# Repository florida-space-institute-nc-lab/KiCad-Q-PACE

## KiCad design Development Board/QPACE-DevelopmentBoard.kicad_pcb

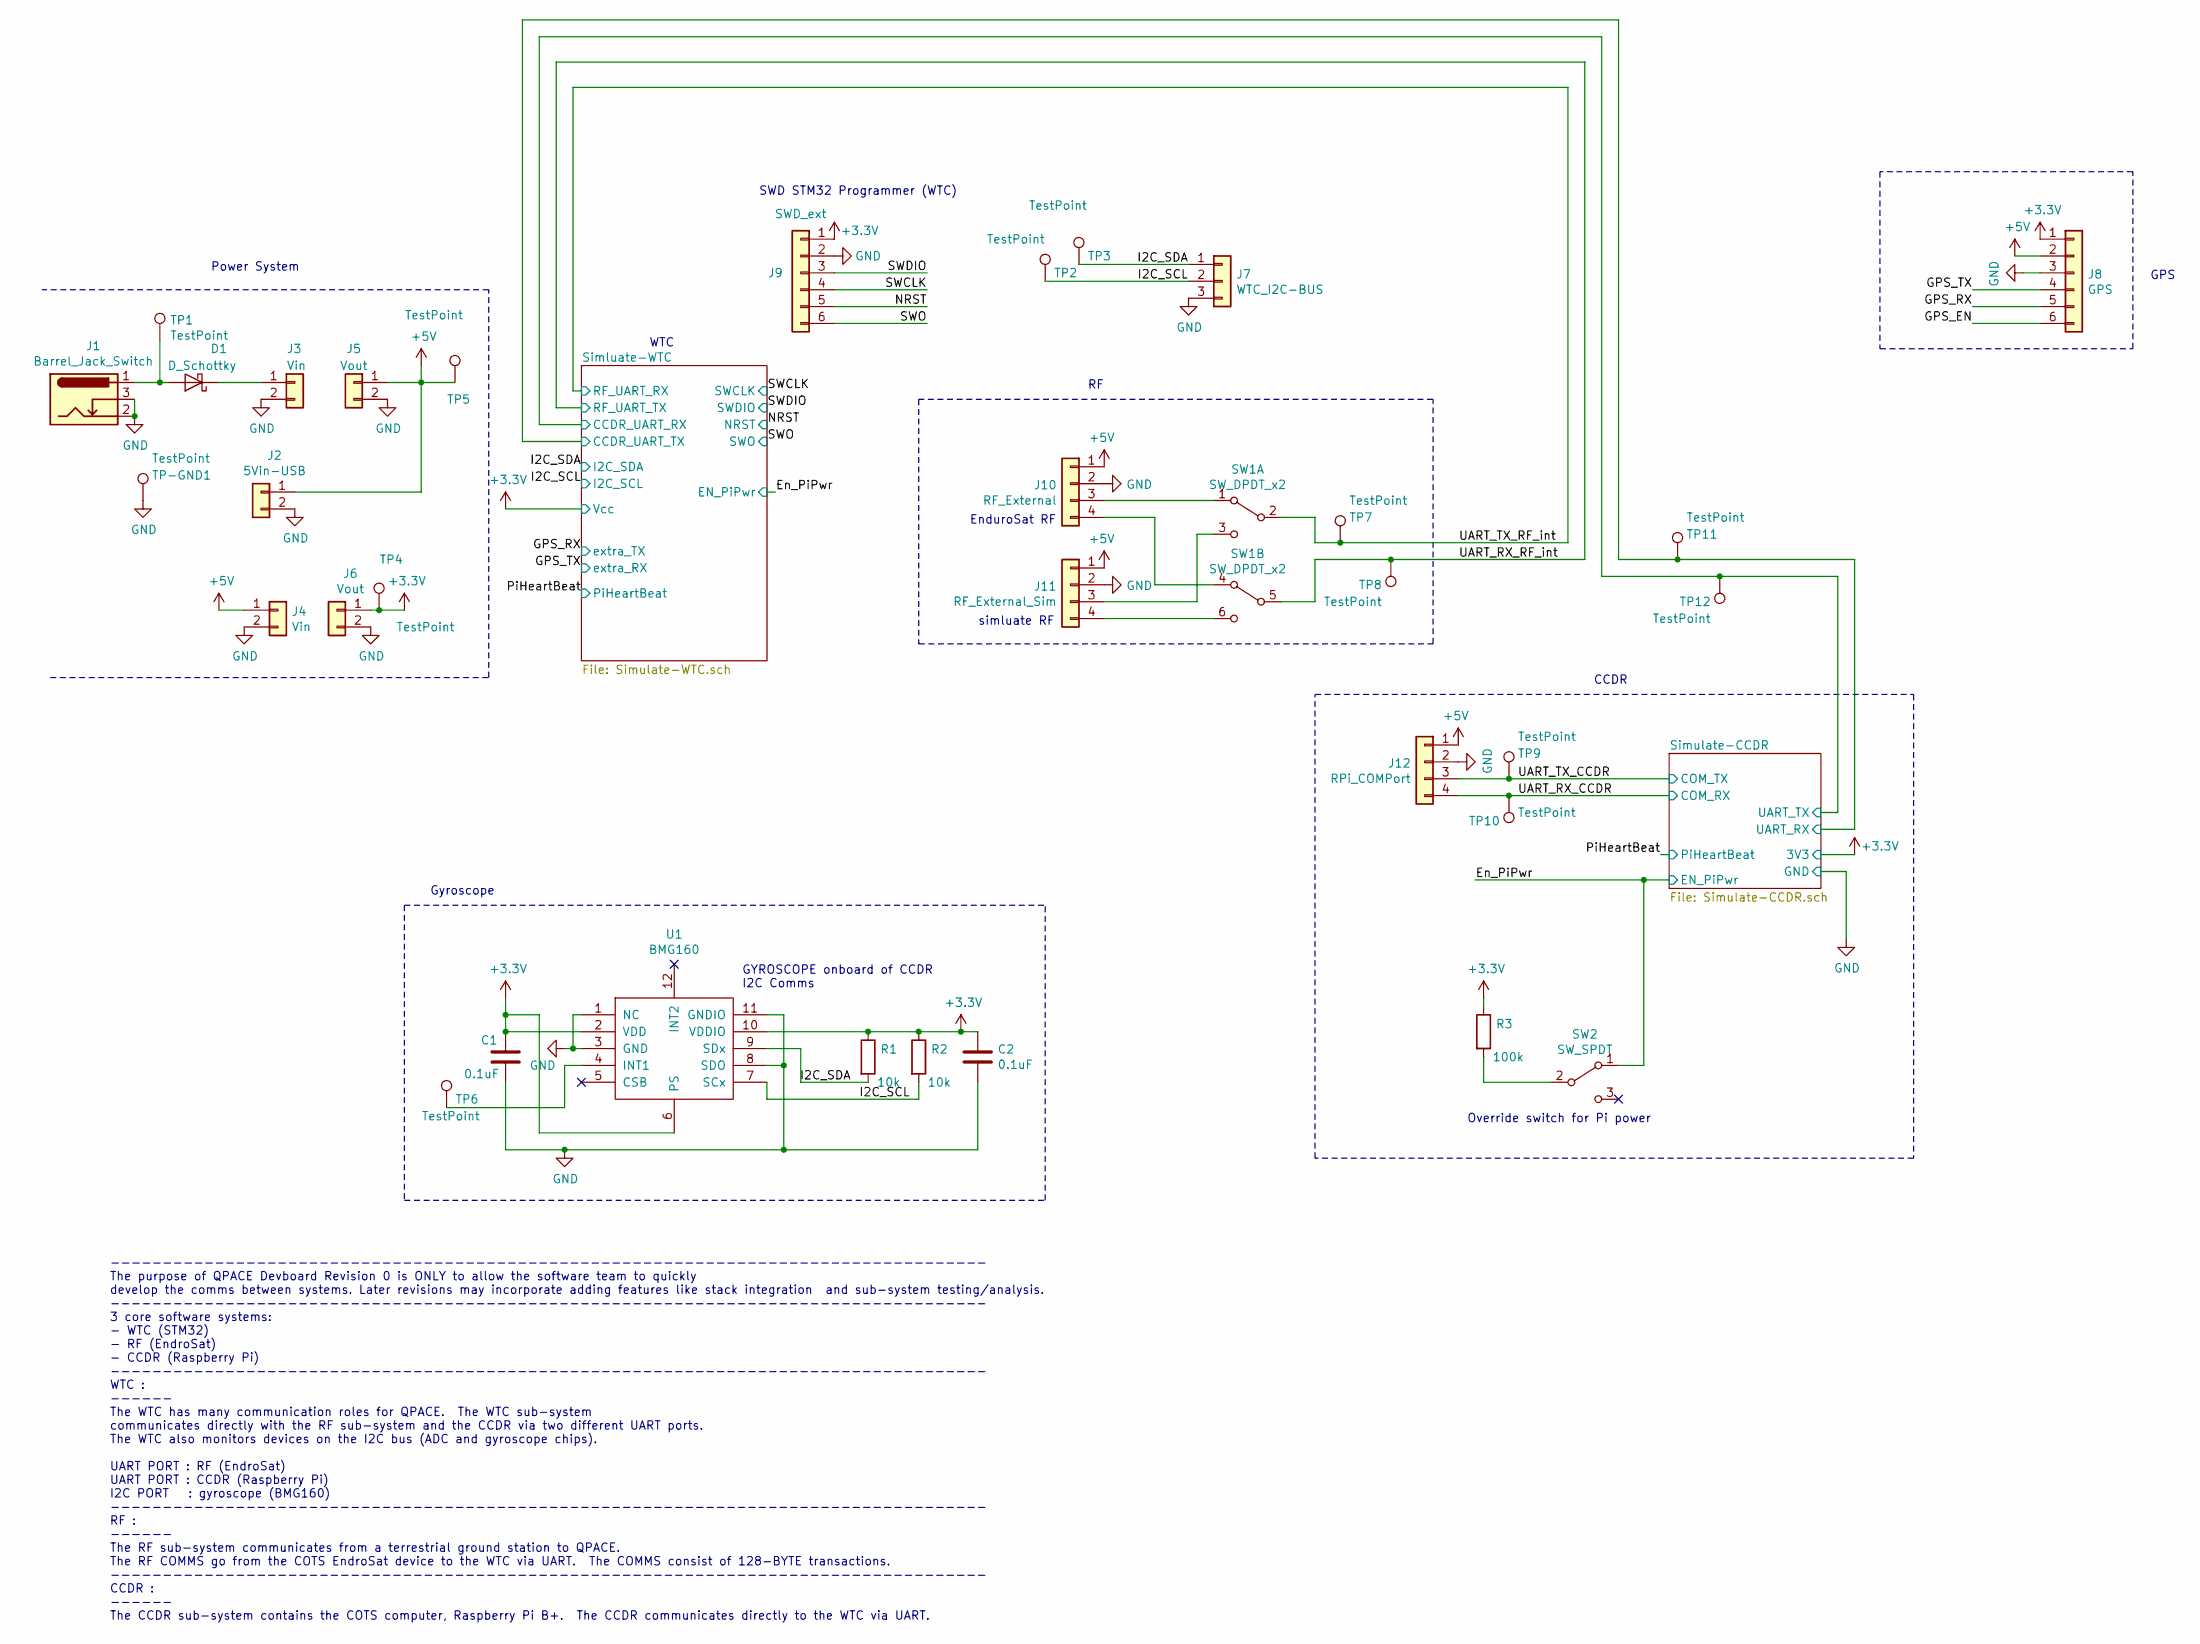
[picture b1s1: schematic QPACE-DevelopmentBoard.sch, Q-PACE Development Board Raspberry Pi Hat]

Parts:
C1, C2: 0.1uF; C_0805
D1: D_Schottky; SOD-128
J1: Barrel_Jack_Switch; TerminalBlock_Phoenix_PT-3.5mm_3pol
J2: 5Vin-USB; Socket_Strip_Straight_1x02_Pitch2.54mm
J3, J4: Vin; Socket_Strip_Straight_1x02_Pitch15.24mm
J5, J6: Vout; Socket_Strip_Straight_1x02_Pitch15.24mm
J7: WTC_I2C-BUS; Socket_Strip_Straight_1x03_Pitch2.54mm
J8: GPS; Socket_Strip_Straight_1x06_Pitch2.54mm
J9: SWD_ext; Socket_Strip_Straight_1x06_Pitch2.54mm
J10: RF_External; Socket_Strip_Straight_1x04_Pitch2.54mm
J11: RF_External_Sim; Socket_Strip_Straight_1x04_Pitch2.54mm
J12: RPi_COMPort; Socket_Strip_Straight_1x04_Pitch2.54mm
R1, R2: 10k; R_0805
R3: 100k; R_0805
SW1: SW_DPDT_x2; Pin_Header_Straight_2x03_Pitch2.54mm
SW2: SW_SPDT; Socket_Strip_Straight_1x03_Pitch2.54mm
TP1, TP2, TP3, TP4, TP5, TP6, TP7, TP8, TP9, TP10, TP11, TP12: TestPoint; Measurement_Point_Round-SMD-Pad_Small
TP-GND1: TestPoint; Measurement_Point_Round-SMD-Pad_Small
U1: BMG160; LGA-12_2x2mm_Pitch0.5mm

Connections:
3_3V_Rail: C1.1, C2.1, J6.1, J8.1, J9.1, R1.1, R2.1, R3.1, TP4.1, U1.2 (VDD), U1.6 (PS), U1.10 (VDDIO); also elsewhere on the board
+5V: J2.1, J4.1, J5.1, J8.2, J10.1, J11.1, J12.1, TP5.1; also elsewhere on the board
/En_PiPwr: SW2.1 (A); also elsewhere on the board
/GPS_RX: J8.5; also elsewhere on the board
/GPS_TX: J8.4; also elsewhere on the board
/I2C_SCL: J7.2, R2.2, TP2.1, U1.7 (SCx); also elsewhere on the board
/I2C_SDA: J7.1, R1.2, TP3.1, U1.9 (SDx); also elsewhere on the board
/NRST: J9.5; also elsewhere on the board
/SWCLK: J9.4; also elsewhere on the board
/SWDIO: J9.3; also elsewhere on the board
/SWO: J9.6; also elsewhere on the board
/Simluate-WTC/CCDR_UART_RX: TP12.1; also elsewhere on the board
/Simluate-WTC/CCDR_UART_TX: TP11.1; also elsewhere on the board
/UART_RX_CCDR: J12.4, TP10.1; also elsewhere on the board
/UART_RX_RF_int: SW1.5 (B), TP8.1; also elsewhere on the board
/UART_TX_CCDR: J12.3, TP9.1; also elsewhere on the board
/UART_TX_RF_int: SW1.2 (B), TP7.1; also elsewhere on the board
GND: C1.2, C2.2, J1.2, J1.3, J2.2, J3.2, J4.2, J5.2, J6.2, J7.3, J8.3, J9.2, J10.2, J11.2, J12.2, TP-GND1.1, U1.1 (NC), U1.3 (GND), U1.8 (SDO), U1.11 (GNDIO); also elsewhere on the board
unnamed: D1.1 (K), J3.1
unnamed: D1.2 (A), J1.1, TP1.1
unnamed: J10.3, SW1.1 (A)
unnamed: J10.4, SW1.4 (A)
unnamed: J11.3, SW1.3 (C)
unnamed: J11.4, SW1.6 (C)
unnamed: R3.2, SW2.2 (B)
unnamed: TP6.1, U1.4 (INT1)

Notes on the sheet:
simluate RF
GYROSCOPE onboard of CCDR I2C Comms
------------------------------------------------------------------------------------ The purpose of QPACE Devboard Revision 0 is ONLY to allow the software team to quickly develop the comms between systems. Later revisions may incorporate adding features like stack integration and sub-system testin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
EnduroSat RF
Power System
WTC
SWD STM32 Programmer (WTC)
CCDR
GPS
Gyroscope
Override switch for Pi power

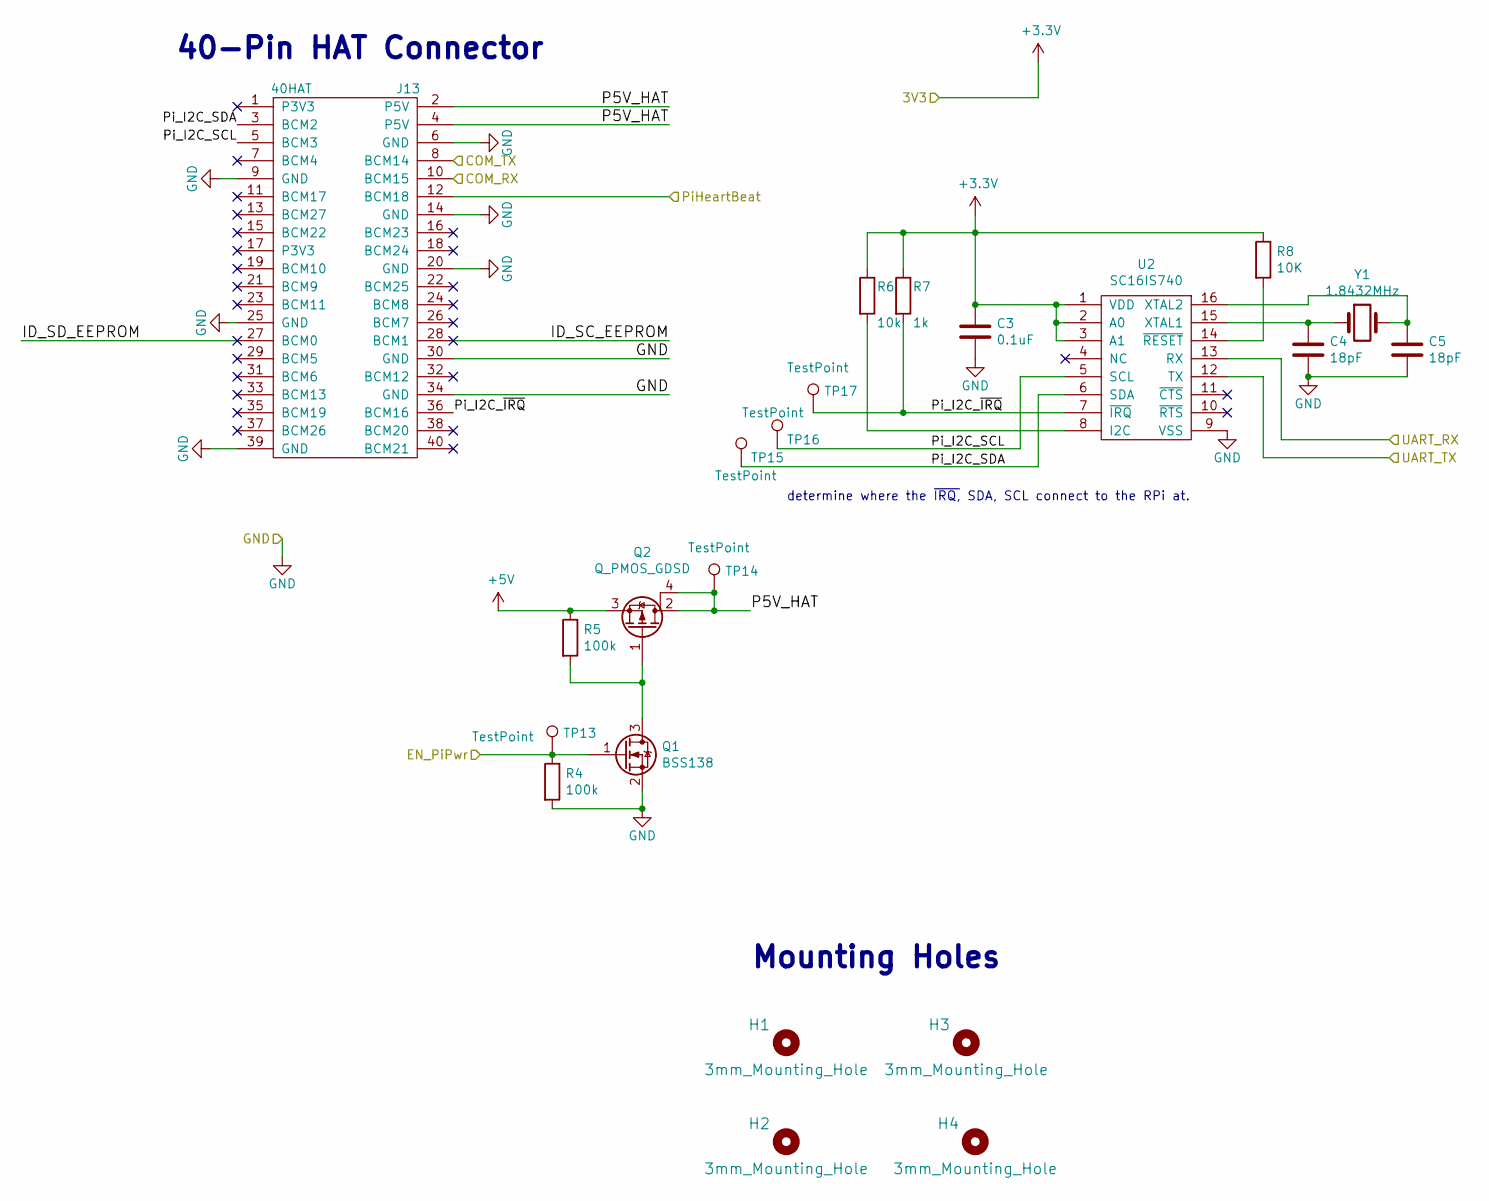
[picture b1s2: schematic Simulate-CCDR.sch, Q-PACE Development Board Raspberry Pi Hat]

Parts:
C3: 0.1uF; C_0805
C4, C5: 18pF; C_0805
H1, H2, H3, H4: 3mm_Mounting_Hole; NPTH_3mm_ID
J13: 40HAT; PinSocket_2x20_P2.54mm_Vertical
Q1: BSS138; SOT-23
Q2: Q_PMOS_GDSD; SOT-223
R4, R5: 100k; R_0805
R6: 10k; R_0805
R7: 1k; R_0805
R8: 10K; R_0805
TP13, TP14, TP15, TP16, TP17: TestPoint; Measurement_Point_Round-SMD-Pad_Small
U2: SC16IS740; TSSOP-16-1EP_4.4x5mm_Pitch0.65mm
Y1: 1.8432MHz; Crystal_HC49-U_Vertical

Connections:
3_3V_Rail: C3.1, R6.1, R7.1, R8.1, U2.1 (VDD), U2.2 (A0), U2.3 (A1); also elsewhere on the board
+5V: Q2.3 (S), R5.1; also elsewhere on the board
/En_PiPwr: Q1.1 (G), R4.1, TP13.1; also elsewhere on the board
/PiHeartBeat: J13.12 (BCM18); also elsewhere on the board
/Simluate-WTC/CCDR_UART_RX: U2.12 (TX); also elsewhere on the board
/Simluate-WTC/CCDR_UART_TX: U2.13 (RX); also elsewhere on the board
/Simulate-CCDR/P5V_HAT: J13.2 (P5V), J13.4 (P5V), Q2.2 (D), Q2.4 (D), TP14.1
/Simulate-CCDR/Pi_I2C_SCL: J13.5 (BCM3), TP16.1, U2.5 (SCL)
/Simulate-CCDR/Pi_I2C_SDA: J13.3 (BCM2), TP15.1, U2.6 (SDA)
/Simulate-CCDR/Pi_I2C_~IRQ: J13.36 (BCM16), R7.2, TP17.1, U2.7 (~IRQ)
/UART_RX_CCDR: J13.10 (BCM15); also elsewhere on the board
/UART_TX_CCDR: J13.8 (BCM14); also elsewhere on the board
GND: C3.2, C4.2, C5.2, J13.6 (GND), J13.9 (GND), J13.14 (GND), J13.20 (GND), J13.25 (GND), J13.30 (GND), J13.34 (GND), J13.39 (GND), Q1.2 (S), R4.2, U2.9 (VSS); also elsewhere on the board
unnamed: C4.1, U2.15 (XTAL1), Y1.1
unnamed: C5.1, U2.16 (XTAL2), Y1.2
unnamed: Q1.3 (D), Q2.1 (G), R5.2
unnamed: R6.2, U2.8 (I2C)
unnamed: R8.2, U2.14 (~RESET)

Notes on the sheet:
Mounting Holes
40-Pin HAT Connector
determine where the ~IRQ, SDA, SCL connect to the RPi at.

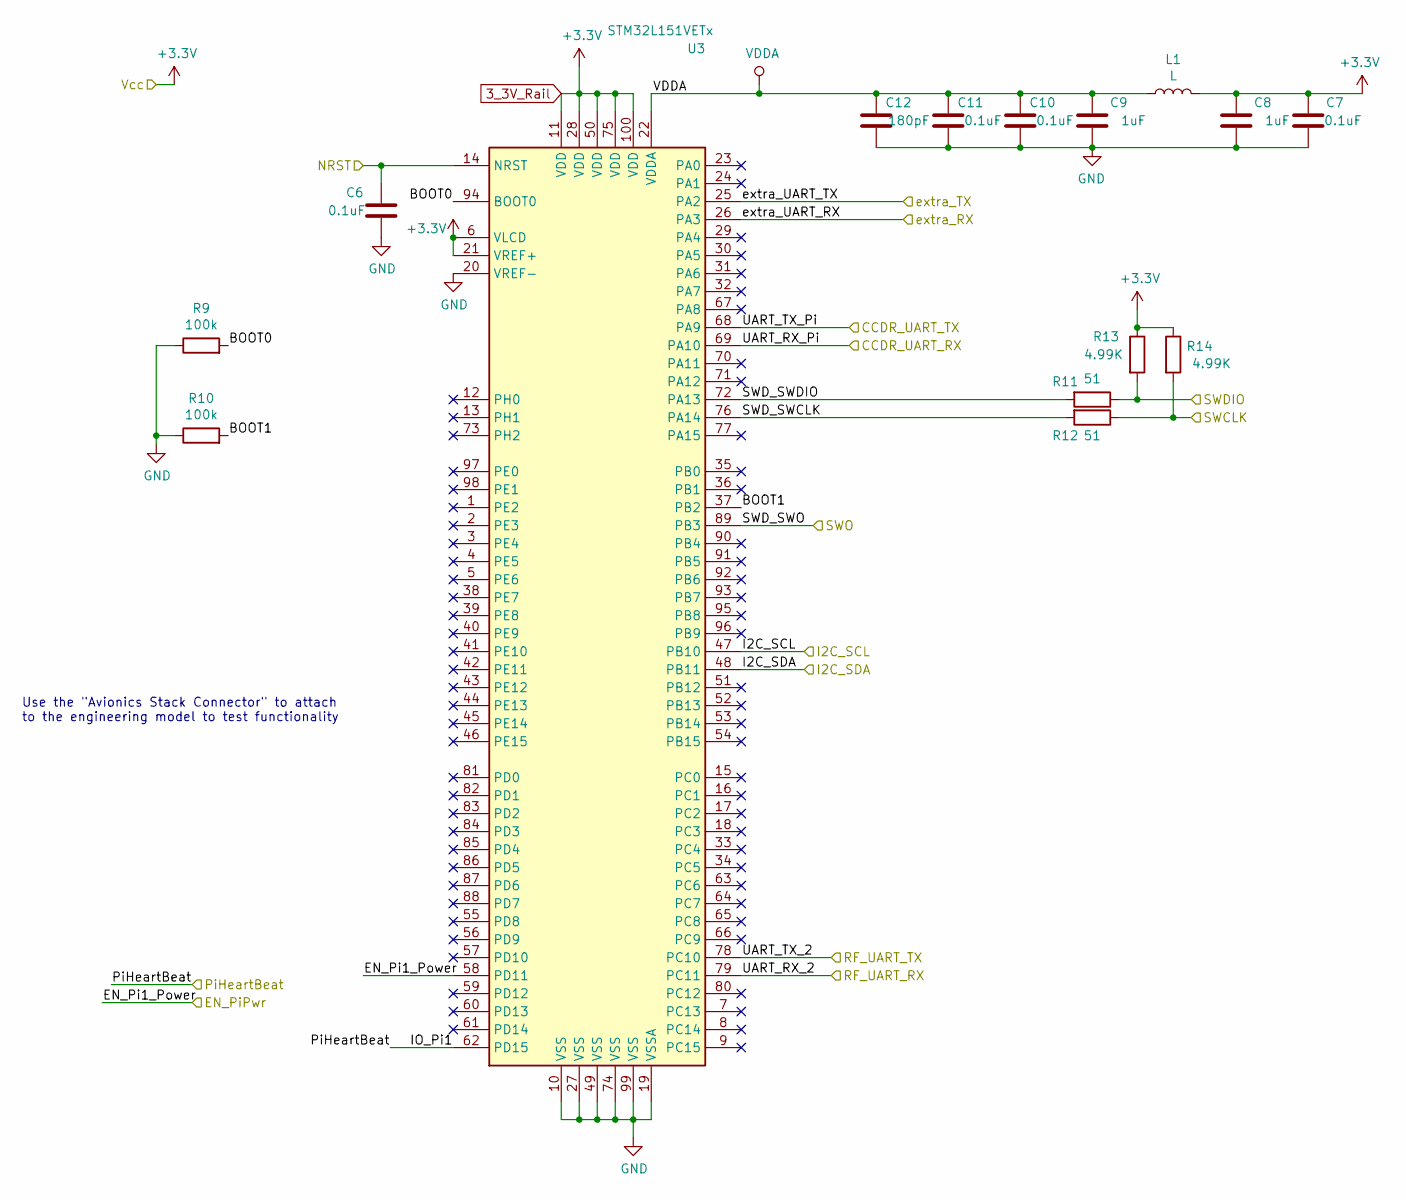
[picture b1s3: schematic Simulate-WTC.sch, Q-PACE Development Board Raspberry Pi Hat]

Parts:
C6, C7, C10, C11: 0.1uF; C_0805
C8, C9: 1uF; C_0805
C12: 180pF; C_0603
L1: L; L_0603
R9, R10: 100k; R_0805
R11, R12: 51; R_0805
R13, R14: 4.99K; R_0805
U3: STM32L151VETx; LQFP-100_14x14mm_Pitch0.5mm

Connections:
3_3V_Rail: C7.1, C8.1, L1.1, R13.1, R14.1, U3.6 (VLCD), U3.11 (VDD), U3.21 (VREF+), U3.28 (VDD), U3.50 (VDD), U3.75 (VDD), U3.100 (VDD); also elsewhere on the board
/En_PiPwr: U3.58 (PD11); also elsewhere on the board
/GPS_RX: U3.25 (PA2); also elsewhere on the board
/GPS_TX: U3.26 (PA3); also elsewhere on the board
/I2C_SCL: U3.47 (PB10); also elsewhere on the board
/I2C_SDA: U3.48 (PB11); also elsewhere on the board
/NRST: C6.1, U3.14 (NRST); also elsewhere on the board
/PiHeartBeat: U3.62 (PD15); also elsewhere on the board
/SWCLK: R12.1, R14.2; also elsewhere on the board
/SWDIO: R11.1, R13.2; also elsewhere on the board
/SWO: U3.89 (PB3); also elsewhere on the board
/Simluate-WTC/BOOT0: R9.2, U3.94 (BOOT0)
/Simluate-WTC/BOOT1: R10.2, U3.37 (PB2)
/Simluate-WTC/CCDR_UART_RX: U3.69 (PA10); also elsewhere on the board
/Simluate-WTC/CCDR_UART_TX: U3.68 (PA9); also elsewhere on the board
/Simluate-WTC/SWD_SWCLK: R12.2, U3.76 (PA14)
/Simluate-WTC/SWD_SWDIO: R11.2, U3.72 (PA13)
/UART_RX_RF_int: U3.78 (PC10); also elsewhere on the board
/UART_TX_RF_int: U3.79 (PC11); also elsewhere on the board
GND: C6.2, C7.2, C8.2, C9.2, C10.2, C11.2, C12.2, R9.1, R10.1, U3.10 (VSS), U3.19 (VSSA), U3.20 (VREF-), U3.27 (VSS), U3.49 (VSS), U3.74 (VSS), U3.99 (VSS); also elsewhere on the board
VDDA: C9.1, C10.1, C11.1, C12.1, L1.2, U3.22 (VDDA)

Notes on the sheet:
Use the "Avionics Stack Connector" to attach to the engineering model to test functionality

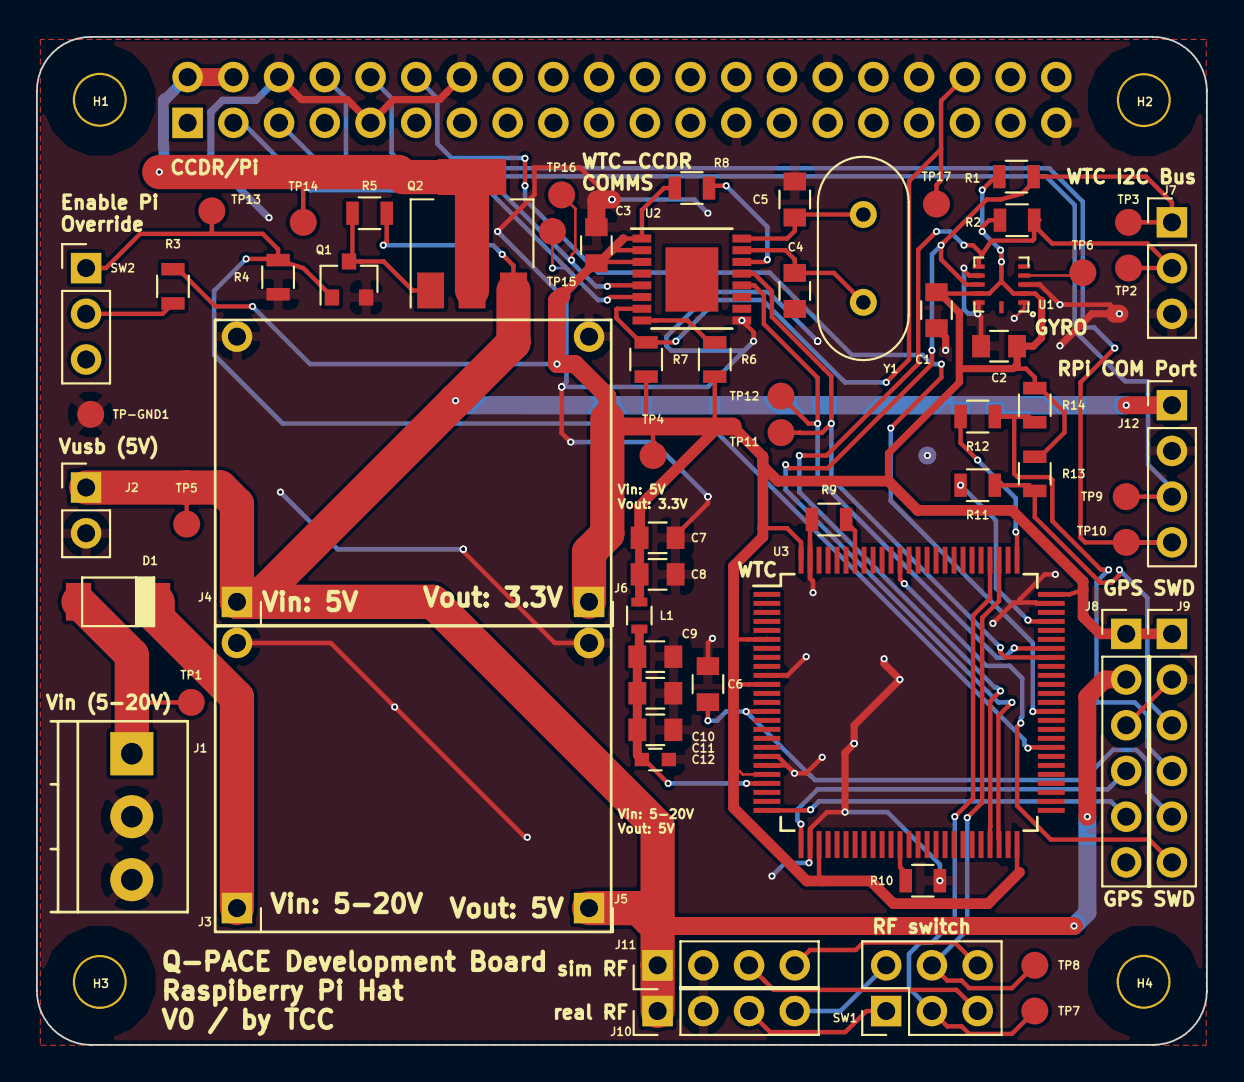
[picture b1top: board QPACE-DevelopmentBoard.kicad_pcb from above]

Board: 4 copper layers, 65.0 x 56.0 mm, 71 parts (1 on the bottom side), 41 nets.

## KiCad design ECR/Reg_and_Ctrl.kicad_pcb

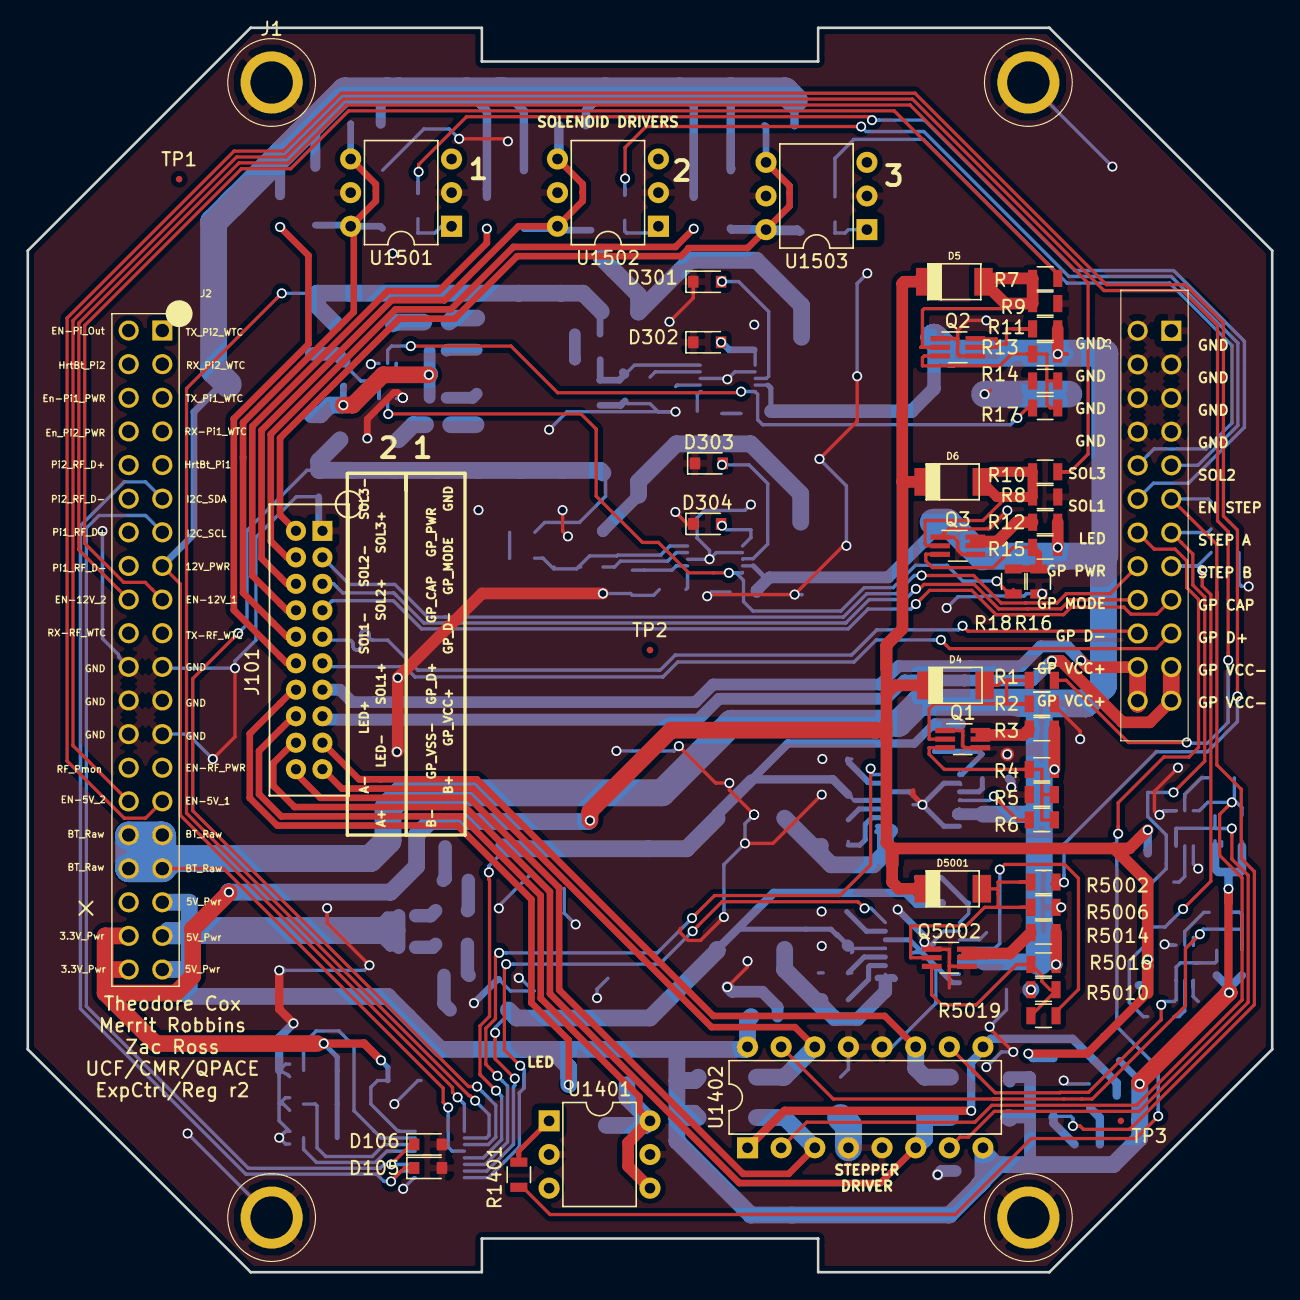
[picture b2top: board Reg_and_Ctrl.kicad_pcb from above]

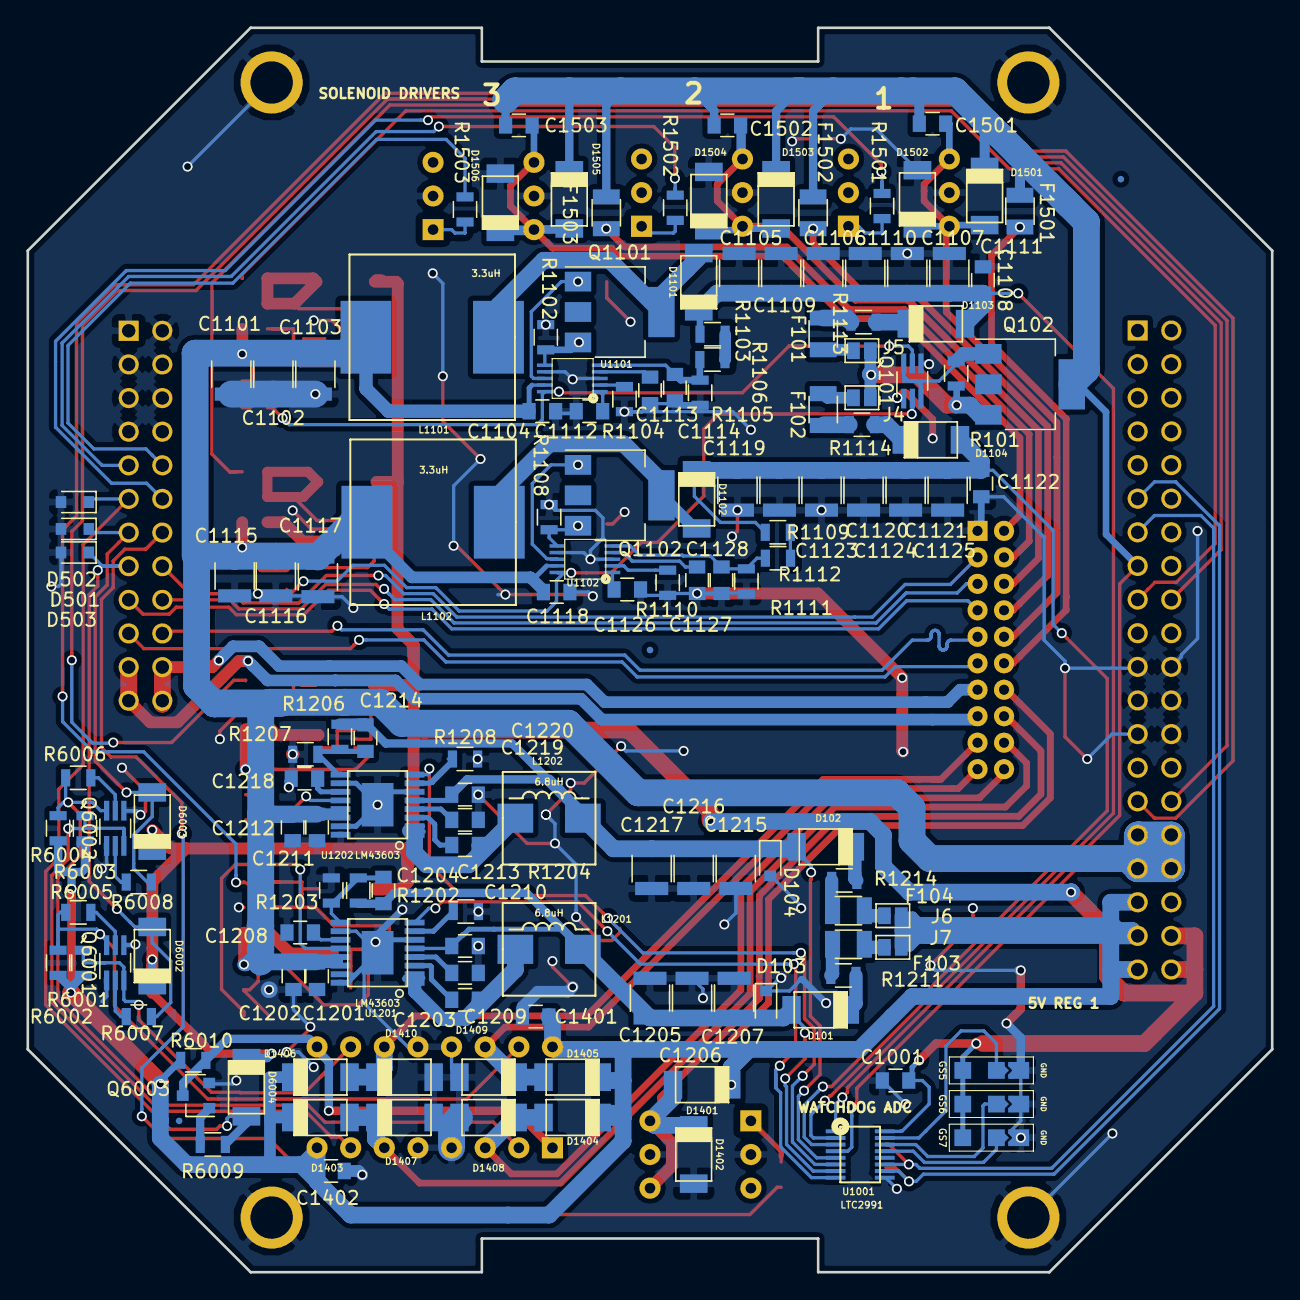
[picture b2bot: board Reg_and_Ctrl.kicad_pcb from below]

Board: 2 copper layers, 94.0 x 94.0 mm, 199 parts (148 on the bottom side), 117 nets.

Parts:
C1001, C1202, C1208, C1212, C1218, C1401, C1402, C1501, C1502, C1503: 0.1uF; C_0805
C1101, C1102, C1103, C1105, C1106, C1107, C1109, C1110, C1111, C1115, C1116, C1117, C1119, C1120, C1121, C1123, C1124, C1125, C1205, C1206, C1207, C1215, C1216, C1217: 47uF; C_1210
C1104, C1118: .1uF; C_0805
C1108, C1112, C1122, C1126: 1uF; C_0805
C1113, C1127: .22uF; C_0805
C1114: 220p; C_0805
C1128: 220pF; C_0805
C1201, C1211: 22uF; C_0805
C1203, C1213: 0.47uF; C_0805
C1204, C1214: 44pF; C_0805
C1209, C1219: 4.7uF; C_0805
C1210, C1220: 2.2uF; C_0805
D4, D5, D6, D5001, D6002, D6003, D6004: D; SOD-128
D101, D102, D1101, D1102, D1103, D1104, D1401, D1402, D1403, D1404, D1405, D1406, D1407, D1408, D1409, D1410, D1501, D1502, D1503, D1504, D1505, D1506: PMEG4030; SOD-128
D103, D104, D105, D106, D301, D302, D303, D304, D501, D502, D503: D_TVS_ALT; D_0805
F101, F102, F103, F104: Polyfuse; Fuse_SMD1206_Reflow
F1501, F1502, F1503: 1206L; Fuse_SMD1206_Reflow
GS5, GS6, GS7: GS3; SolderBridge_0805
J1: Board Mount; boardMount_0125in060
J2: Qpace_40-Pin_Connector; Samtec_SSQ-120-03-G-D_QPACE_40-Pin_r1
J3: CCDR; Samtec_SSQ-112-03-G-D
J4, J5, J6, J7: GS2
J101: LS2-110-01-L-D
L1101, L1102: 3.3uH; DR125-IND
L1201, L1202: 6.8uH; 744314650_6.5uH
Q1, Q2, Q3, Q101, Q5002, Q6001, Q6002: BSS138-Dual; SOT-363_SC-70-6_Handsoldering
Q102: Q_PMOS_GDS; SOT-223-4_GDS
Q1101, Q1102: Q_NMOS_GDS; SOT-223-4_GDS
Q6003: BSS138; SOT-23
R1, R3, R4, R7, R8, R11, R12, R13, R15, R101, R5002, R5014, R5016, R6001, R6002, R6003, R6004, R6005, R6006, R6007, R6008, R6009, R6010: 100K; R_0805
R2, R5, R9, R10, R14, R16, R5006, R5010: 1M; R_0805
R6, R17, R18, R5019: 1K; R_0805
R1102, R1108: 0.01; R_0805
R1103, R1109: 200k 0.1%; R_0805
R1104, R1110: 100k; R_0805
R1105, R1111: 24.9k 0.1%; R_0805
R1106, R1112: 18k 0.1%; R_0805
R1113, R1114: 0.1 1%; R_0805
R1202, R1206: 1M 0.1%; R_0805
R1203, R1207: 249k 0.1%; R_0805
R1204, R1208: 50K; R_0805
R1211, R1214: 0.1 1% 0.25W; R_0805
R1401, R1501, R1502, R1503: 1k; R_0805
TP1, TP2, TP3: TEST; Fiducial_0.5mm_Dia_1mm_Outer_FB
U1001: LTC2991; LTC2991_MSOP_16
U1101, U1102: MAX668
U1201, U1202: LM43603; LM43603_HTSSOP-16
U1401, U1501, U1502, U1503: V014642_A; DIP-6_W7.62mm
U1402: SN754410_A; DIP-16_W7.62mm

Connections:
3.3V_Pwr: C1001.1, D4.2, D5.2, D6.2, D5001.2, D6002.2, D6003.2, D6004.2, GS5.3, GS6.3, GS7.3, J2.38, J2.40, U1001.16
5V_Pwr: C1401.2, C1402.1, D1401.2, D1403.2, D1404.2, D1405.2, D1406.2, J2.35, J2.37, J2.39, J6.2, J7.2, J101.14, R6001.2, R6002.1, R6003.2, R6004.1, R6010.2, U1402.8, U1402.16
5V_Rail_1_Enable: J2.29, R5002.1
5V_Rail_2_Enable: J2.30, R1.1
12V_1_Enable: J2.17, R7.1
12V_2_Enable: J2.18, R8.1
12V_Pwr: C1501.1, C1502.1, C1503.1, D1501.2, D1503.2, D1505.2, F1501.2, F1502.2, F1503.2, J2.15, Q102.2, U1001.1
/5V_MOV_2: C1204.1, C1205.1, C1206.1, C1207.1, C1210.1, D101.1, D103.2, L1201.2, R1202.1, U1001.7, U1201.5
/5V_MOV_4: C1214.1, C1215.1, C1216.1, C1217.1, C1220.1, D102.1, D104.1, L1202.2, R1206.1, U1001.5, U1202.5
/12V Rail Regulators/12V_MOV_1: D301.2, Q1101.1, U1101.8
/12V Rail Regulators/12V_MOV_2: D302.2, Q1101.3, R1102.2, U1101.6
/12V Rail Regulators/12V_MOV_3: D303.2, Q1102.1, U1102.8
/12V Rail Regulators/12V_MOV_4: D304.2, Q1102.3, R1108.2, U1102.6
/12V_Balanced: J4.1, J5.2, Q102.3, R101.1
/12V_Out_1: C1105.1, C1106.1, C1107.1, C1108.1, C1109.1, C1110.1, C1111.1, D1101.2, D1103.1, R1103.2, U1001.2
/12V_Out_2: C1119.1, C1120.1, C1121.1, C1122.1, C1123.1, C1124.1, C1125.1, D1102.2, D1104.1, R1109.2, U1001.3
/A+_Out: D1404.1, D1408.2, J101.20, U1402.3
/A-_Out: D1403.1, D1407.2, J101.18, U1402.6
/B+_Out: D1405.1, D1409.2, J101.19, U1402.14
/B-_Out: D1406.1, D1410.2, J101.17, U1402.11
/EN_REGS/EN_5V_1: R5019.2, U1201.12
/EN_REGS/EN_5V_2: R6.2, U1202.12
/En_12V1: Q101.5, R17.2, U1101.10
/En_12V2: Q101.2, R18.2, U1102.10
/LED-: D1401.1, D1402.2, J101.16, U1401.4, U1401.6
/Sol_1+: F1501.1, J101.12
/Sol_1-: C1501.2, D1501.1, D1502.2, J101.10, U1501.4, U1501.6
/Sol_2+: F1502.1, J101.8
/Sol_2-: C1502.2, D1503.1, D1504.2, J101.6, U1502.4, U1502.6
/Sol_3+: F1503.1, J101.4
/Sol_3-: C1503.2, D1505.1, D1506.2, J101.2, U1503.4, U1503.6
/Stepper_Driver/EN_Stepper(out): Q6003.3, R6010.1, U1402.1, U1402.9
/Stepper_Driver/Step_A+: Q6002.6, R6004.2, R6006.2, U1402.2
/Stepper_Driver/Step_A-: Q6002.3, R6003.1, U1402.7
/Stepper_Driver/Step_B+: Q6001.6, R6002.2, R6005.2, U1402.15
/Stepper_Driver/Step_B-: Q6001.3, R6001.1, U1402.10
BT_Raw: C1101.1, C1102.1, C1103.1, C1104.1, C1115.1, C1116.1, C1117.1, C1118.1, C1201.1, C1202.1, C1211.1, C1212.1, J2.31, J2.32, J2.33, J2.34, L1101.1, L1102.1, R3.2, R4.2, R11.2, R12.2, R13.2, R15.1, R5014.2, R5016.2, U1001.4, U1101.9, U1102.9, U1201.13, U1201.14, U1202.13, U1202.14
GND: C1001.2, C1101.2, C1102.2, C1103.2, C1104.2, C1105.2, C1106.2, C1107.2, C1108.2, C1109.2, C1110.2, C1111.2, C1112.2, C1113.2, C1114.1, C1115.2, C1116.2, C1117.2, C1118.2, C1119.2, C1120.2, C1121.2, C1122.2, C1123.2, C1124.2, C1125.2, C1126.2, C1127.2, C1128.1, C1201.2, C1202.2, C1205.2, C1206.2, C1207.2, C1208.2, C1209.2, C1210.2, C1211.2, C1212.2, C1215.2, C1216.2, C1217.2, C1218.2, C1219.2, C1220.2, C1401.1, C1402.2, D103.1, D104.2, D105.2, D106.2, D301.1, D302.1, D303.1, D304.1, D501.2, D502.2, D503.2, D1402.1, D1407.1, D1408.1, D1409.1, D1410.1, D1502.1, D1504.1, D1506.1, GS5.1, GS6.1, GS7.1, J1.1, J1.2, J1.3, J1.4, J2.21, J2.22, J2.23, J2.24, J2.25, J2.26, J3.1, J3.2, J3.3, J3.4, J3.5, J3.6, J3.7, J3.8, J101.1, Q1.1, Q1.4, Q2.1, Q2.4, Q3.1, Q3.4, Q101.1, Q101.4, Q5002.1, Q5002.4, Q6001.1, Q6001.4, Q6002.1, Q6002.4, Q6003.2, R2.2, R5.2, R9.2, R10.2, R14.2, R16.2, R1102.1, R1104.2, R1105.2, R1108.1, R1110.2, R1111.2, R1203.2, R1204.2, R1207.2, R1208.2, R5006.2, R5010.2, U1001.9, U1101.3, U1101.7, U1102.3, U1102.7, U1201.6, U1201.10, U1201.15, U1201.16, U1201.17, U1202.6, U1202.10, U1202.15, U1202.16, U1202.17, U1401.2, U1401.5, U1402.4, U1402.5, U1402.12, U1402.13, U1501.2, U1501.5, U1502.2, U1502.5, U1503.2, U1503.5
GoPro+: J3.22, J3.24, J101.13
GoPro-: J3.21, J3.23, J101.15
GoPro_Capture: J3.17, J101.7
GoPro_Mode: J3.18, J101.5
GoPro_Power: J3.16, J101.3
GoPro_USB_D+: J3.19, J101.11
GoPro_USB_D-: J3.20, J101.9
I2C_SCL: D106.1, J2.13, U1001.11
I2C_SDA: D105.1, J2.11, U1001.10
LED_Ctrl: J3.14, R1401.2
MOV_PIN1: D501.1, D6003.1, J3.13, R6008.2
MOV_PIN2: D503.1, D6002.1, J3.15, R6007.2
MOV_PIN3: D502.1, D6004.1, J3.11, R6009.2
unnamed: C1112.1, U1101.1
unnamed: C1113.1, U1101.4
unnamed: C1114.2, R1105.1, R1106.1, U1101.5
unnamed: C1126.1, U1102.1
unnamed: C1127.1, U1102.4
unnamed: C1128.2, R1111.1, R1112.1, U1102.5
unnamed: C1203.1, L1201.1, U1201.1, U1201.2
unnamed: C1203.2, U1201.3
unnamed: C1204.2, R1202.2, R1203.1, U1201.9
unnamed: C1208.1, U1201.11
unnamed: C1209.1, U1201.4
unnamed: C1213.1, L1202.1, U1202.1, U1202.2
unnamed: C1213.2, U1202.3
unnamed: C1214.2, R1206.2, R1207.1, U1202.9
unnamed: C1218.1, U1202.11
unnamed: C1219.1, U1202.4
unnamed: D4.1, Q1.2, R1.2, R2.1
unnamed: D5.1, Q2.2, R7.2, R9.1
unnamed: D6.1, Q3.2, R8.2, R10.1
unnamed: D101.2, R1211.1
unnamed: D102.2, R1214.1
unnamed: D1101.1, L1101.2, Q1101.2
unnamed: D1102.1, L1102.2, Q1102.2
unnamed: D1103.2, R1113.1
unnamed: D1104.2, R1114.1
unnamed: D5001.1, Q5002.2, R5002.2, R5006.1
unnamed: F101.1, J5.1
unnamed: F101.2, R1113.2
unnamed: F102.1, J4.2
unnamed: F102.2, R1114.2
unnamed: F103.1, J6.1
unnamed: F103.2, R1211.2
unnamed: F104.1, J7.1
unnamed: F104.2, R1214.2
unnamed: GS5.2, U1001.15
unnamed: GS6.2, U1001.14
unnamed: GS7.2, U1001.13
unnamed: Q1.3, R4.1, R5.1, R6.1
unnamed: Q1.5, Q1.6, R3.1
unnamed: Q2.3, R13.1, R14.1, R17.1
unnamed: Q2.5, Q2.6, R11.1
unnamed: Q3.3, R15.2, R16.1, R18.1
unnamed: Q3.5, Q3.6, R12.1
unnamed: Q101.3, Q101.6, Q102.1, R101.2
unnamed: Q5002.3, R5010.1, R5014.1, R5019.1
unnamed: Q5002.5, Q5002.6, R5016.1
unnamed: Q6001.2, R6007.1
unnamed: Q6001.5, R6005.1
unnamed: Q6002.2, R6008.1
unnamed: Q6002.5, R6006.1
unnamed: Q6003.1, R6009.1
unnamed: R1103.1, R1106.2
unnamed: R1104.1, U1101.2
unnamed: R1109.1, R1112.2
unnamed: R1110.1, U1102.2
unnamed: R1204.1, U1201.7
unnamed: R1208.1, U1202.7
unnamed: R1401.1, U1401.1
unnamed: R1501.1, U1501.1
unnamed: R1502.1, U1502.1
unnamed: R1503.1, U1503.1
PGOOD_5V1: U1001.8, U1201.8
PGOOD_5V2: U1001.6, U1202.8
Sol_Ctrl_1: J3.12, R1501.2
Sol_Ctrl_2: J3.9, R1502.2
Sol_Ctrl_3: J3.10, R1503.2
